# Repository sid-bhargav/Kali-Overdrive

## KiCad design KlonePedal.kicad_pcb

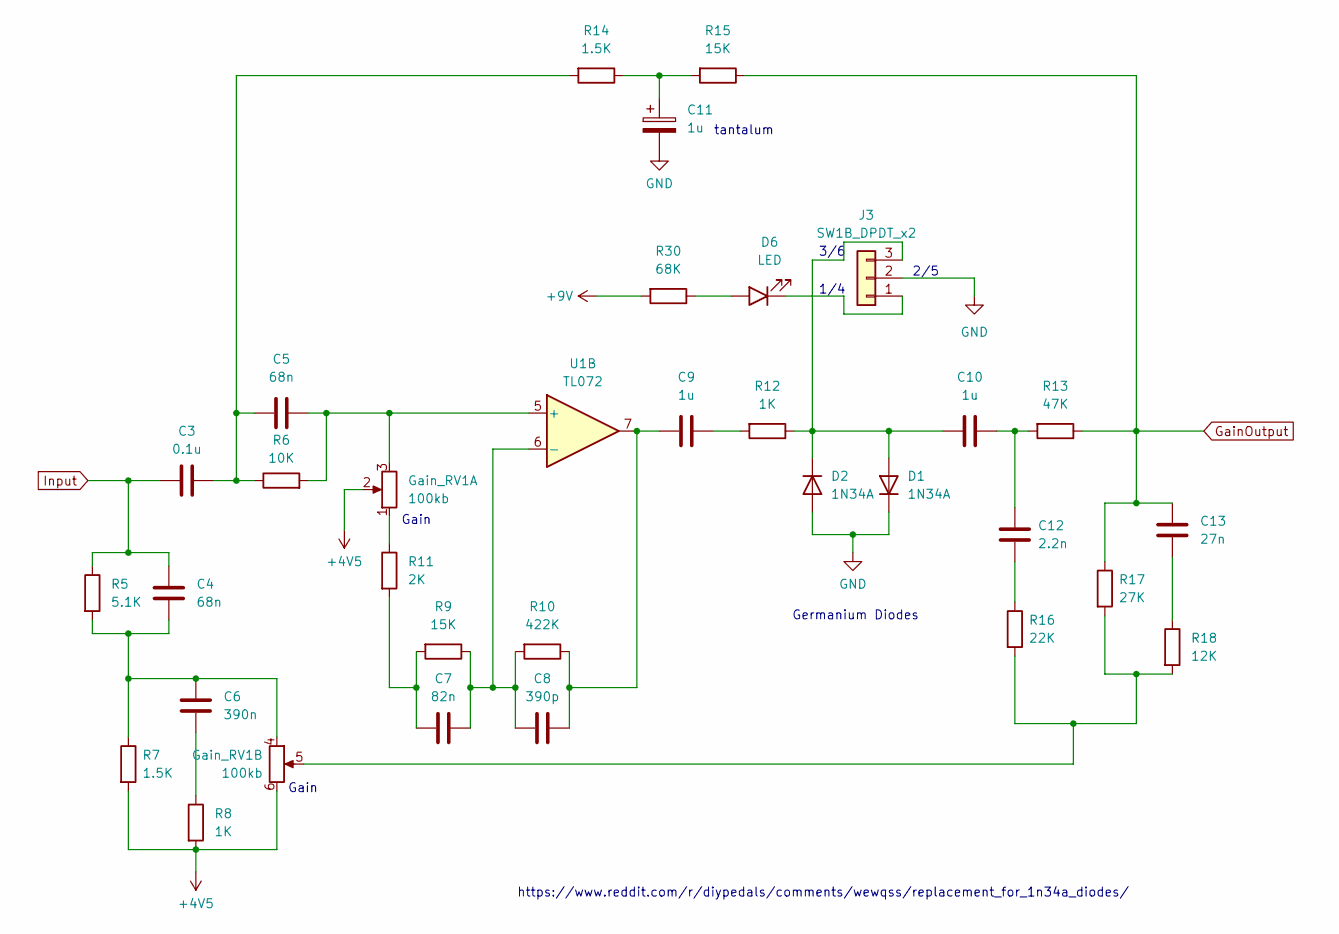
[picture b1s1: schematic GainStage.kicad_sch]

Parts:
C3: 0.1u; C_0805_2012Metric_Pad1.18x1.45mm_HandSolder
C4, C5: 68n; C_0805_2012Metric_Pad1.18x1.45mm_HandSolder
C6: 390n; C_0805_2012Metric_Pad1.18x1.45mm_HandSolder
C7: 82n; C_0805_2012Metric_Pad1.18x1.45mm_HandSolder
C8: 390p; C_0805_2012Metric_Pad1.18x1.45mm_HandSolder
C9, C10, C11: 1u; C_0805_2012Metric_Pad1.18x1.45mm_HandSolder
C12: 2.2n; C_0805_2012Metric_Pad1.18x1.45mm_HandSolder
C13: 27n; C_0805_2012Metric_Pad1.18x1.45mm_HandSolder
D1, D2: 1N34A; D_DO-41_SOD81_P10.16mm_Horizontal
D6: LED; LED_D3.0mm
Gain_RV1: 100kb; P0925N
J3: SW1B_DPDT_x2; JST_XH_S3B-XH-A_1x03_P2.50mm_Horizontal
R5: 5.1K; R_0805_2012Metric_Pad1.20x1.40mm_HandSolder
R6: 10K; R_0805_2012Metric_Pad1.20x1.40mm_HandSolder
R7, R14: 1.5K; R_0805_2012Metric_Pad1.20x1.40mm_HandSolder
R8, R12: 1K; R_0805_2012Metric_Pad1.20x1.40mm_HandSolder
R9, R15: 15K; R_0805_2012Metric_Pad1.20x1.40mm_HandSolder
R10: 422K; R_0805_2012Metric_Pad1.20x1.40mm_HandSolder
R11: 2K; R_0805_2012Metric_Pad1.20x1.40mm_HandSolder
R13: 47K; R_0805_2012Metric_Pad1.20x1.40mm_HandSolder
R16: 22K; R_0805_2012Metric_Pad1.20x1.40mm_HandSolder
R17: 27K; R_0805_2012Metric_Pad1.20x1.40mm_HandSolder
R18: 12K; R_0805_2012Metric_Pad1.20x1.40mm_HandSolder
R30: 68K; R_0805_2012Metric_Pad1.20x1.40mm_HandSolder
U1: TL072; SO-8_3.9x4.9mm_P1.27mm

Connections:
+4V5: Gain_RV1.2, Gain_RV1.6, R7.2, R8.2; also elsewhere on the board
+9V: R30.2; also elsewhere on the board
GND: C11.2, D1.1 (K), D2.2 (A), J3.2; also elsewhere on the board
GainOutput: C13.2, R13.1, R15.1, R17.1; also elsewhere on the board
Input: C3.1, C4.2, R5.1; also elsewhere on the board
unnamed: C3.2, C5.1, R6.1, R14.2
unnamed 11: C4.1, C6.2, Gain_RV1.4, R5.2, R7.1; also elsewhere on the board
unnamed: C6.1, R8.1
unnamed: C7.2, R9.2, R11.2
unnamed: C8.1, C9.2, R10.1, U1.7
unnamed: C9.1, R12.2
unnamed: C10.1, C12.1, R13.2
unnamed: C11.1, R14.1, R15.2
unnamed: C12.2, R16.1
unnamed: C13.1, R18.1
unnamed: C10.2, D1.2 (A), D2.1 (K), J3.3, R12.1
unnamed: D6.2 (A), R30.1
unnamed: D6.1 (K), J3.1
unnamed 27: Gain_RV1.1, R11.1; also elsewhere on the board
unnamed 28: Gain_RV1.5, R16.2, R17.2, R18.2; also elsewhere on the board
unnamed 37: C5.2, Gain_RV1.3, R6.2, U1.5 (+); also elsewhere on the board
unnamed: C7.1, C8.2, R9.1, R10.2, U1.6 (-)

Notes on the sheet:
Germanium Diodes
Gain
3/6
1/4
Gain
2/5
tantalum
https://www.reddit.com/r/diypedals/comments/wewqss/replacement_for_1n34a_diodes/

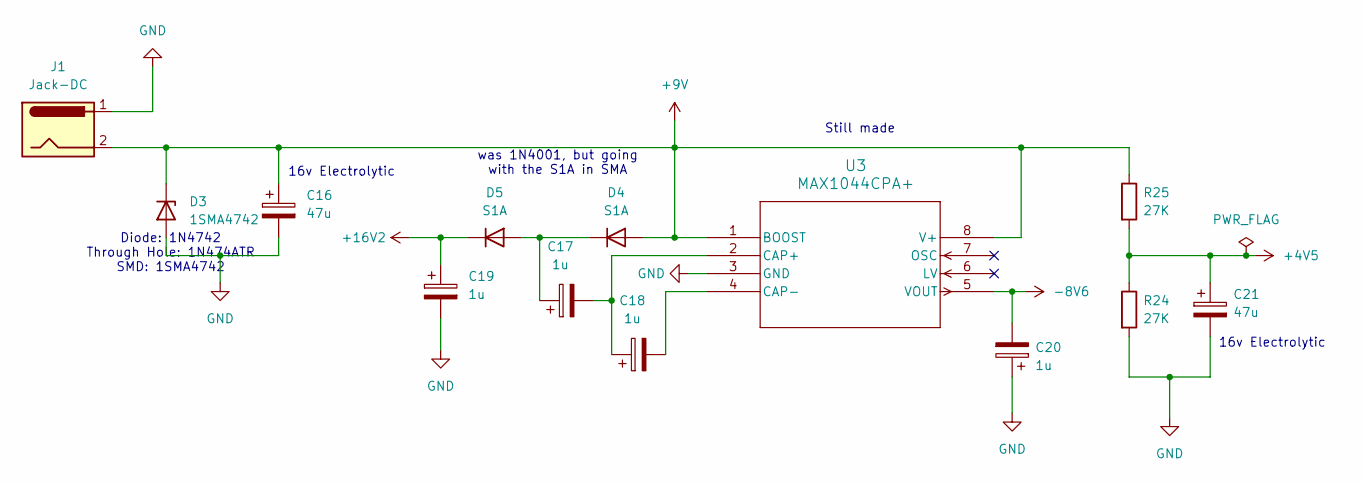
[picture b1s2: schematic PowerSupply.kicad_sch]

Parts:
C16, C21: 47u; CP_Elec_5x5.4
C17, C18, C19, C20: 1u; CP_Elec_4x5.4
D3: 1SMA4742; D_SMA_Handsoldering
D4, D5: S1A; D_SMA_Handsoldering
J1: Jack-DC; CUI_PJ-037A
R24, R25: 27K; R_0805_2012Metric_Pad1.20x1.40mm_HandSolder
U3: MAX1044CPA+; SO-8_3.9x4.9mm_P1.27mm

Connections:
+4V5: C21.1, R24.1, R25.2; also elsewhere on the board
+9V: C16.1, D3.1 (K), D4.2 (A), J1.2, R25.1, U3.1 (BOOST), U3.8 (V+); also elsewhere on the board
+16V2: C19.1, D5.1 (K); also elsewhere on the board
-8V6: C20.2, U3.5 (VOUT); also elsewhere on the board
GND: C16.2, C19.2, C20.1, C21.2, D3.2 (A), J1.1, R24.2, U3.3 (GND); also elsewhere on the board
unnamed: C17.1, D4.1 (K), D5.2 (A)
unnamed: C17.2, C18.1, U3.2 (CAP+)
unnamed: C18.2, U3.4 (CAP-)

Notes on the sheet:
16v Electrolytic
was 1N4001, but going with the S1A in SMA
Still made
Diode: 1N4742 Through Hole: 1N474ATR SMD: 1SMA4742

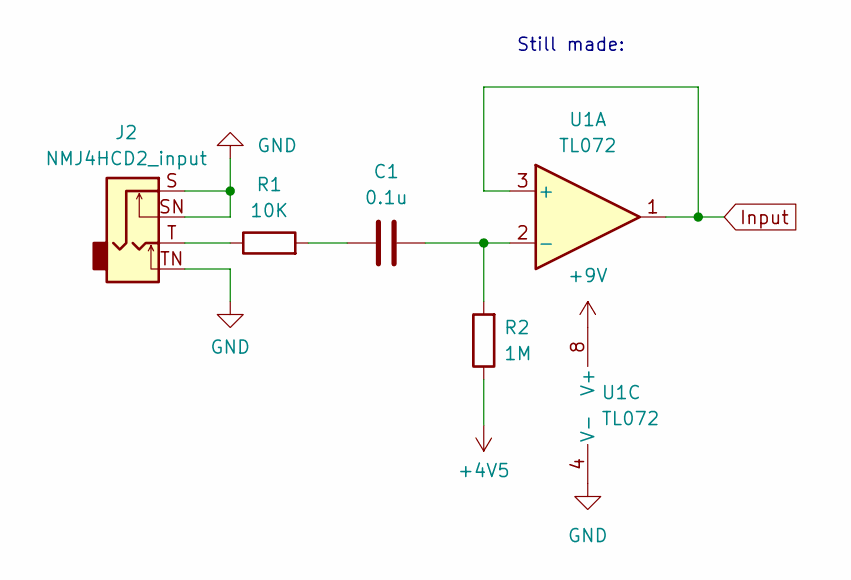
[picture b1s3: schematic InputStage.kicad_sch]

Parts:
C1: 0.1u; C_0805_2012Metric_Pad1.18x1.45mm_HandSolder
J2: NMJ4HCD2_input; Jack_6.35mm_Neutrik_NMJ4HCD2_Horizontal
R1: 10K; R_0805_2012Metric_Pad1.20x1.40mm_HandSolder
R2: 1M; R_0805_2012Metric_Pad1.20x1.40mm_HandSolder
U1: TL072; SO-8_3.9x4.9mm_P1.27mm

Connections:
+4V5: R2.1; also elsewhere on the board
+9V: U1.8 (V+); also elsewhere on the board
GND: J2.S, J2.SN, J2.TN, U1.4 (V-); also elsewhere on the board
Input: U1.1, U1.3 (+); also elsewhere on the board
unnamed: C1.1, R1.2
unnamed 29: J2.T, R1.1; also elsewhere on the board
unnamed: C1.2, R2.2, U1.2 (-)

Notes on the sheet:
Still made:

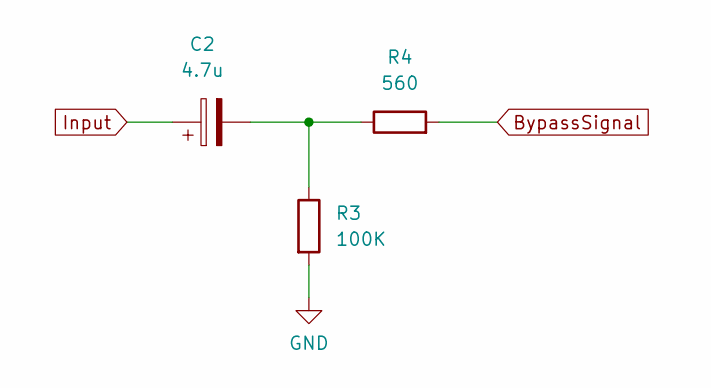
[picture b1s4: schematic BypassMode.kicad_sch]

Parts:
C2: 4.7u; C_0805_2012Metric_Pad1.18x1.45mm_HandSolder
R3: 100K; R_0805_2012Metric_Pad1.20x1.40mm_HandSolder
R4: 560; R_0805_2012Metric_Pad1.20x1.40mm_HandSolder

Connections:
BypassSignal: R4.2; also elsewhere on the board
GND: R3.2; also elsewhere on the board
Input: C2.1; also elsewhere on the board
unnamed: C2.2, R3.1, R4.1

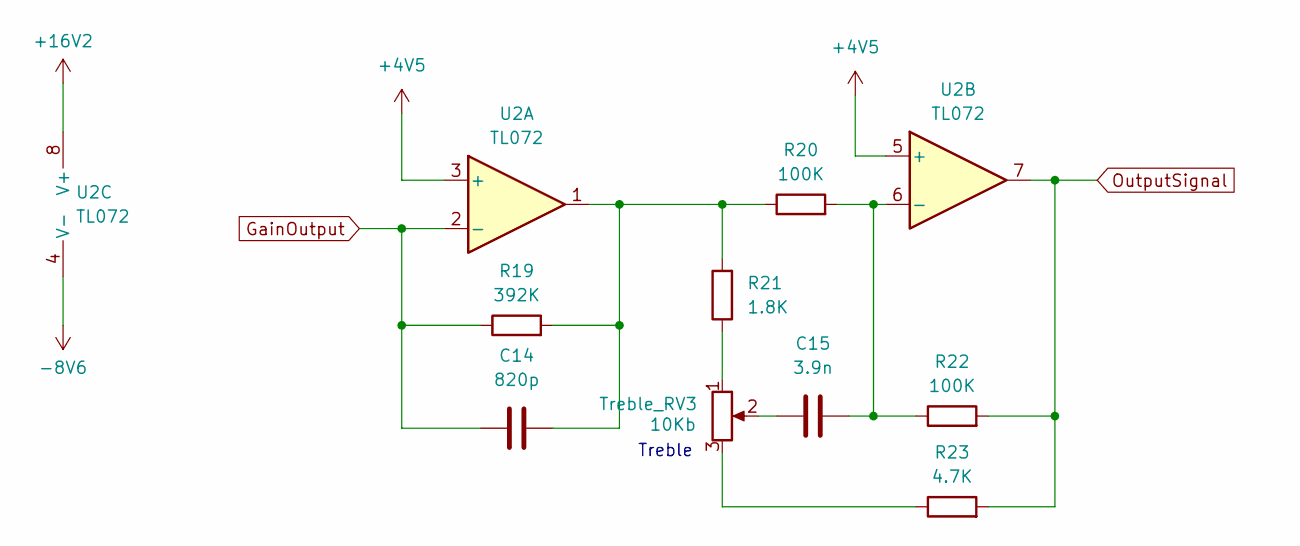
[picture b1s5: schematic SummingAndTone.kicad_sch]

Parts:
C14: 820p; C_0805_2012Metric_Pad1.18x1.45mm_HandSolder
C15: 3.9n; C_0805_2012Metric_Pad1.18x1.45mm_HandSolder
R19: 392K; R_0805_2012Metric_Pad1.20x1.40mm_HandSolder
R20, R22: 100K; R_0805_2012Metric_Pad1.20x1.40mm_HandSolder
R21: 1.8K; R_0805_2012Metric_Pad1.20x1.40mm_HandSolder
R23: 4.7K; R_0805_2012Metric_Pad1.20x1.40mm_HandSolder
Treble_RV3: 10Kb; P0915N
U2: TL072; SO-8_3.9x4.9mm_P1.27mm

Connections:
+4V5: U2.3 (+), U2.5 (+); also elsewhere on the board
+16V2: U2.8 (V+); also elsewhere on the board
-8V6: U2.4 (V-); also elsewhere on the board
GainOutput: C14.1, R19.1, U2.2 (-); also elsewhere on the board
unnamed: C14.2, R19.2, R20.1, R21.2, U2.1
unnamed 21: C15.1, Treble_RV3.2; also elsewhere on the board
unnamed 34: R21.1, Treble_RV3.1; also elsewhere on the board
unnamed 35: R23.1, Treble_RV3.3; also elsewhere on the board
unnamed: C15.2, R20.2, R22.1, U2.6 (-)
OutputSignal: R22.2, R23.2, U2.7; also elsewhere on the board

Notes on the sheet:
Treble

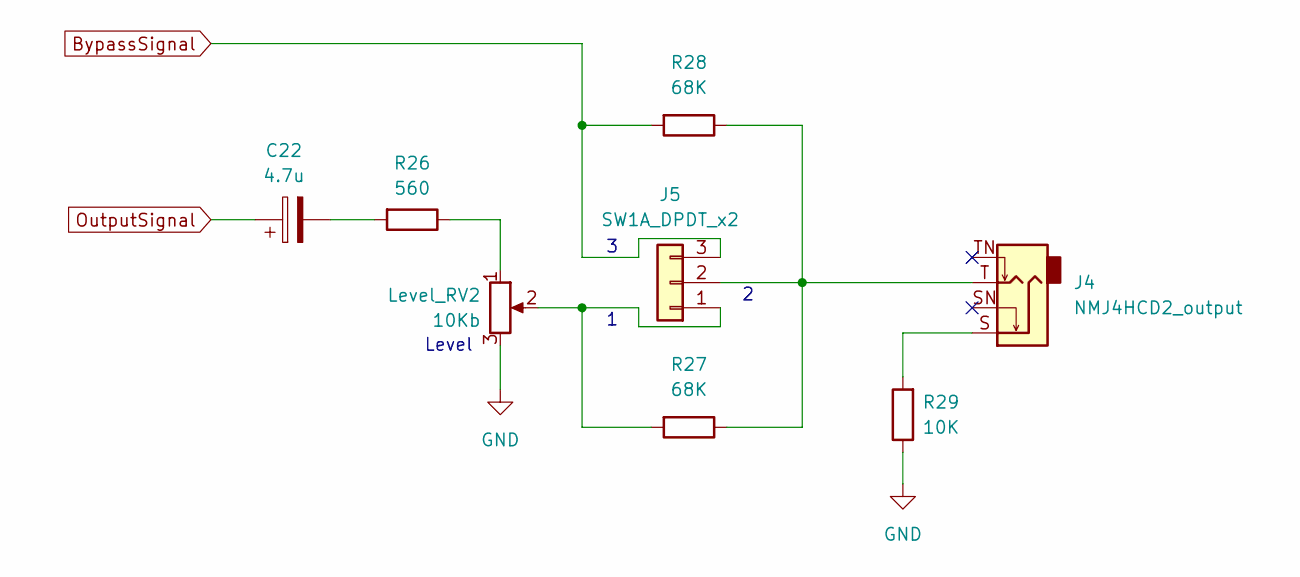
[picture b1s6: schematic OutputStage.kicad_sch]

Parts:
C22: 4.7u; C_0805_2012Metric_Pad1.18x1.45mm_HandSolder
J4: NMJ4HCD2_output; Jack_6.35mm_Neutrik_NMJ4HCD2_Horizontal
J5: SW1A_DPDT_x2; JST_XH_S3B-XH-A_1x03_P2.50mm_Horizontal
Level_RV2: 10Kb; P0915N
R26: 560; R_0805_2012Metric_Pad1.20x1.40mm_HandSolder
R27, R28: 68K; R_0805_2012Metric_Pad1.20x1.40mm_HandSolder
R29: 10K; R_0805_2012Metric_Pad1.20x1.40mm_HandSolder

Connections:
BypassSignal: J5.3, R28.2; also elsewhere on the board
GND: Level_RV2.3, R29.1; also elsewhere on the board
unnamed: C22.2, R26.2
unnamed 30: J4.S, R29.2; also elsewhere on the board
unnamed 31: J5.1, Level_RV2.2, R27.2; also elsewhere on the board
unnamed 32: J4.T, J5.2, R27.1, R28.1; also elsewhere on the board
unnamed 33: Level_RV2.1, R26.1; also elsewhere on the board
OutputSignal: C22.1; also elsewhere on the board

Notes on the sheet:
Level

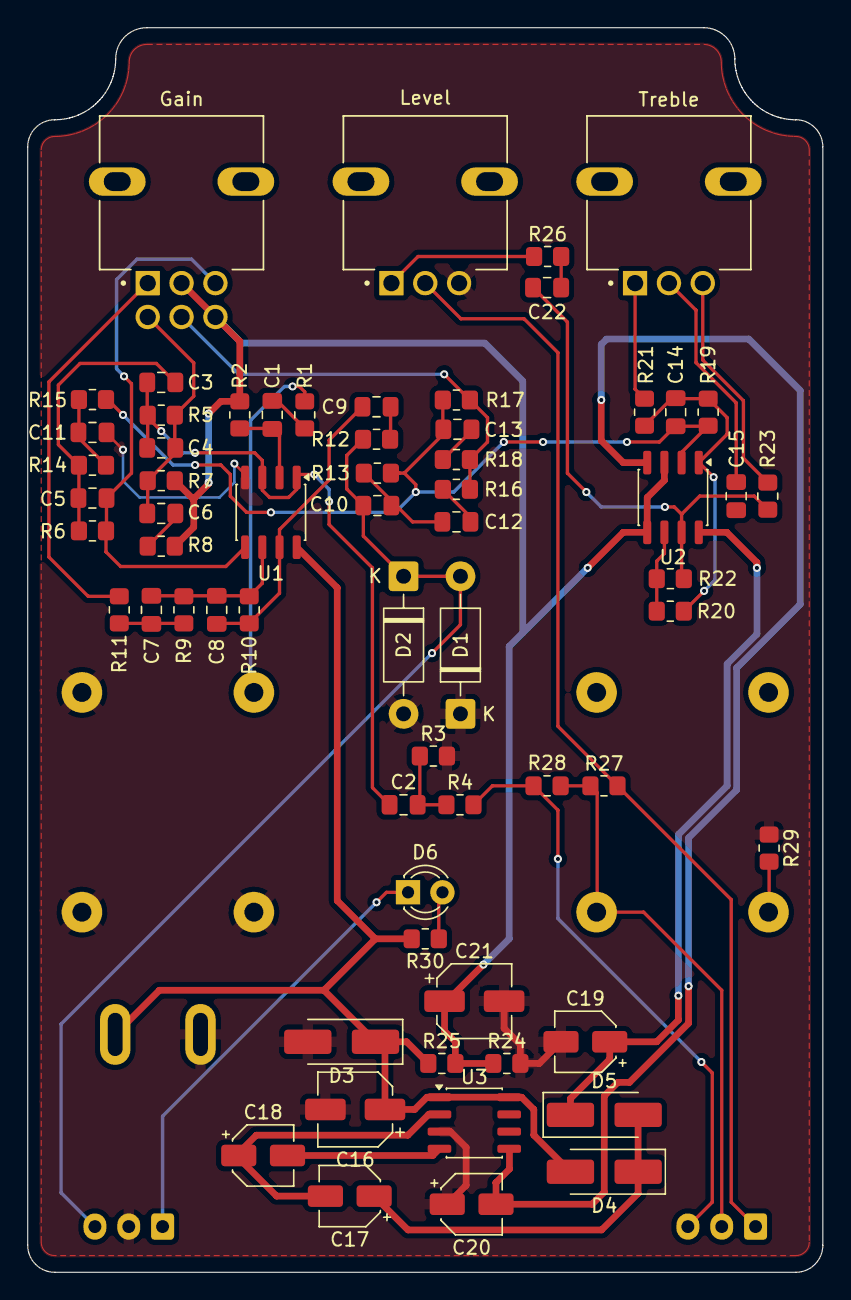
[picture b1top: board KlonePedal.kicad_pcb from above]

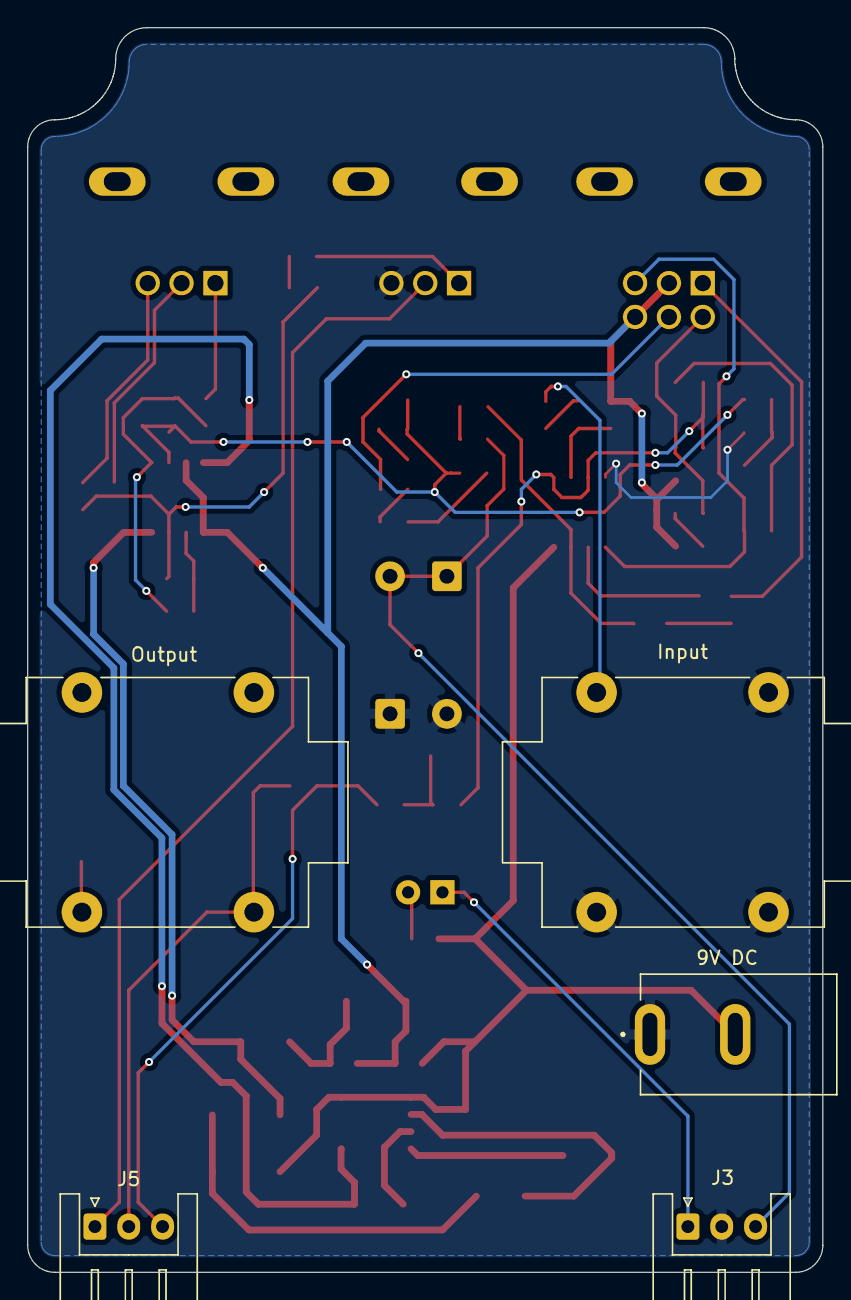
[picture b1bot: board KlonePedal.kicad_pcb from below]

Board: 2 copper layers, 58.7 x 91.9 mm, 69 parts (5 on the bottom side), 43 nets.

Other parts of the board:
9V DC: Jack-DC; CUI_PJ-037A
Gain: 100kb; P0925N
Input: NMJ4HCD2_input; Jack_6.35mm_Neutrik_NMJ4HCD2_Horizontal
Level: 10Kb; P0915N
Output: NMJ4HCD2_output; Jack_6.35mm_Neutrik_NMJ4HCD2_Horizontal
Treble: 10Kb; P0915N

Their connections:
+4V5: Gain.2, Gain.6; also elsewhere on the board
+9V: 9V DC.2; also elsewhere on the board
GND: 9V DC.1, Input.S, Input.SN, Input.TN, Level.3; also elsewhere on the board
unnamed 11: Gain.4; also elsewhere on the board
unnamed 21: Treble.2; also elsewhere on the board
unnamed 27: Gain.1; also elsewhere on the board
unnamed 28: Gain.5; also elsewhere on the board
unnamed 29: Input.T; also elsewhere on the board
unnamed 30: Output.S; also elsewhere on the board
unnamed 31: Level.2; also elsewhere on the board
unnamed 32: Output.T; also elsewhere on the board
unnamed 33: Level.1; also elsewhere on the board
unnamed 34: Treble.1; also elsewhere on the board
unnamed 35: Treble.3; also elsewhere on the board
unnamed 37: Gain.3; also elsewhere on the board

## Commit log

2026-04-09 initial design
2026-04-09 using smt caps and resistors
2026-04-10 change metal film resistor footprint
2026-04-11 add all smd components
2026-04-11 First routing of power circuit
2026-04-18 Updated PCB Outline
2026-04-19 initial layout
2026-04-19 Added ground pours
2026-04-20 Changed silkscreen font
